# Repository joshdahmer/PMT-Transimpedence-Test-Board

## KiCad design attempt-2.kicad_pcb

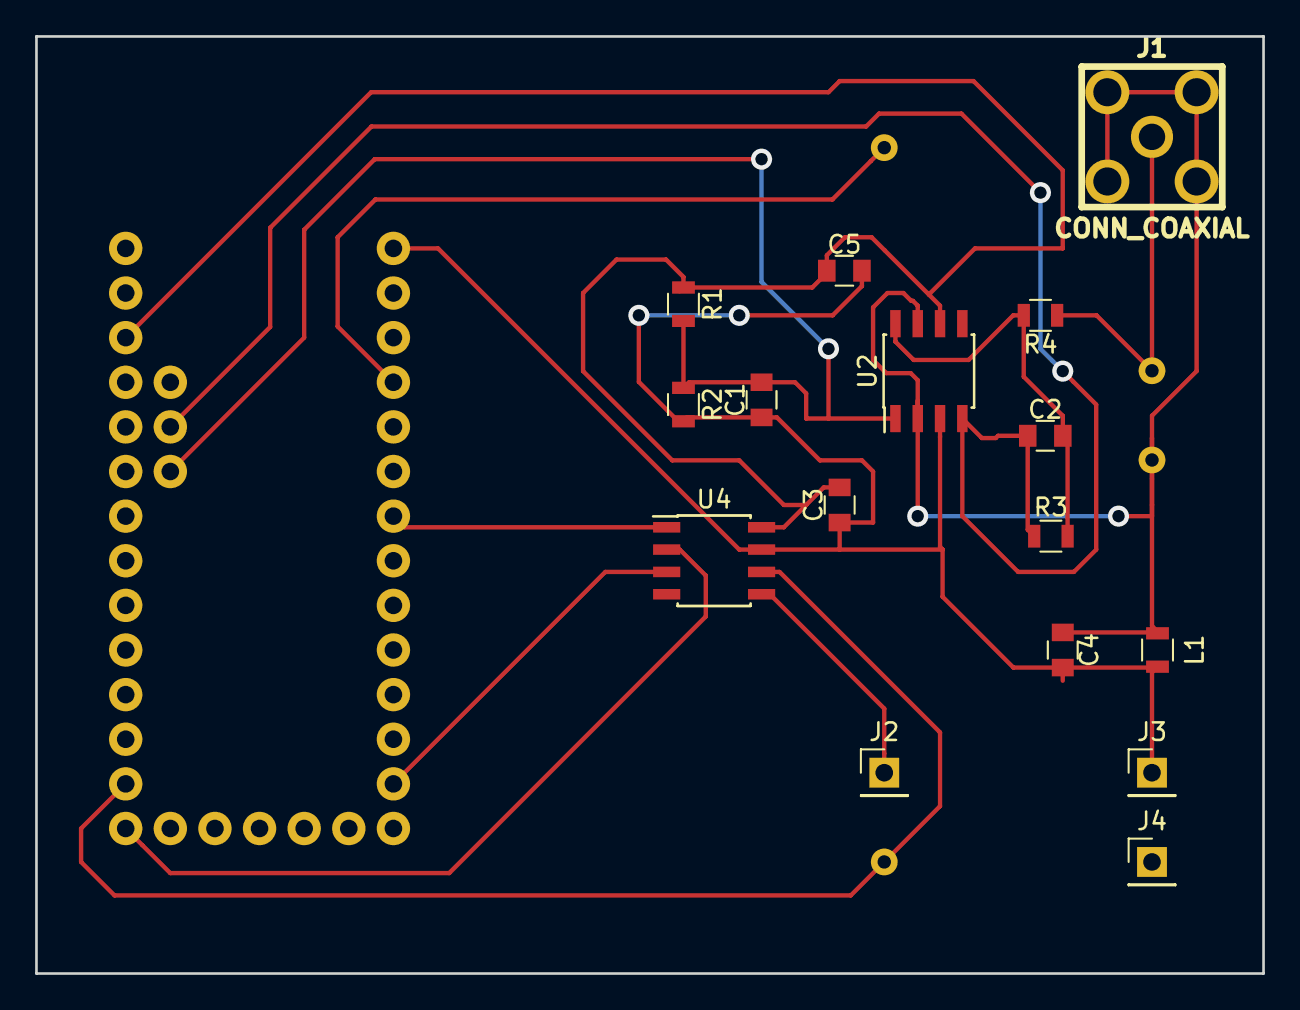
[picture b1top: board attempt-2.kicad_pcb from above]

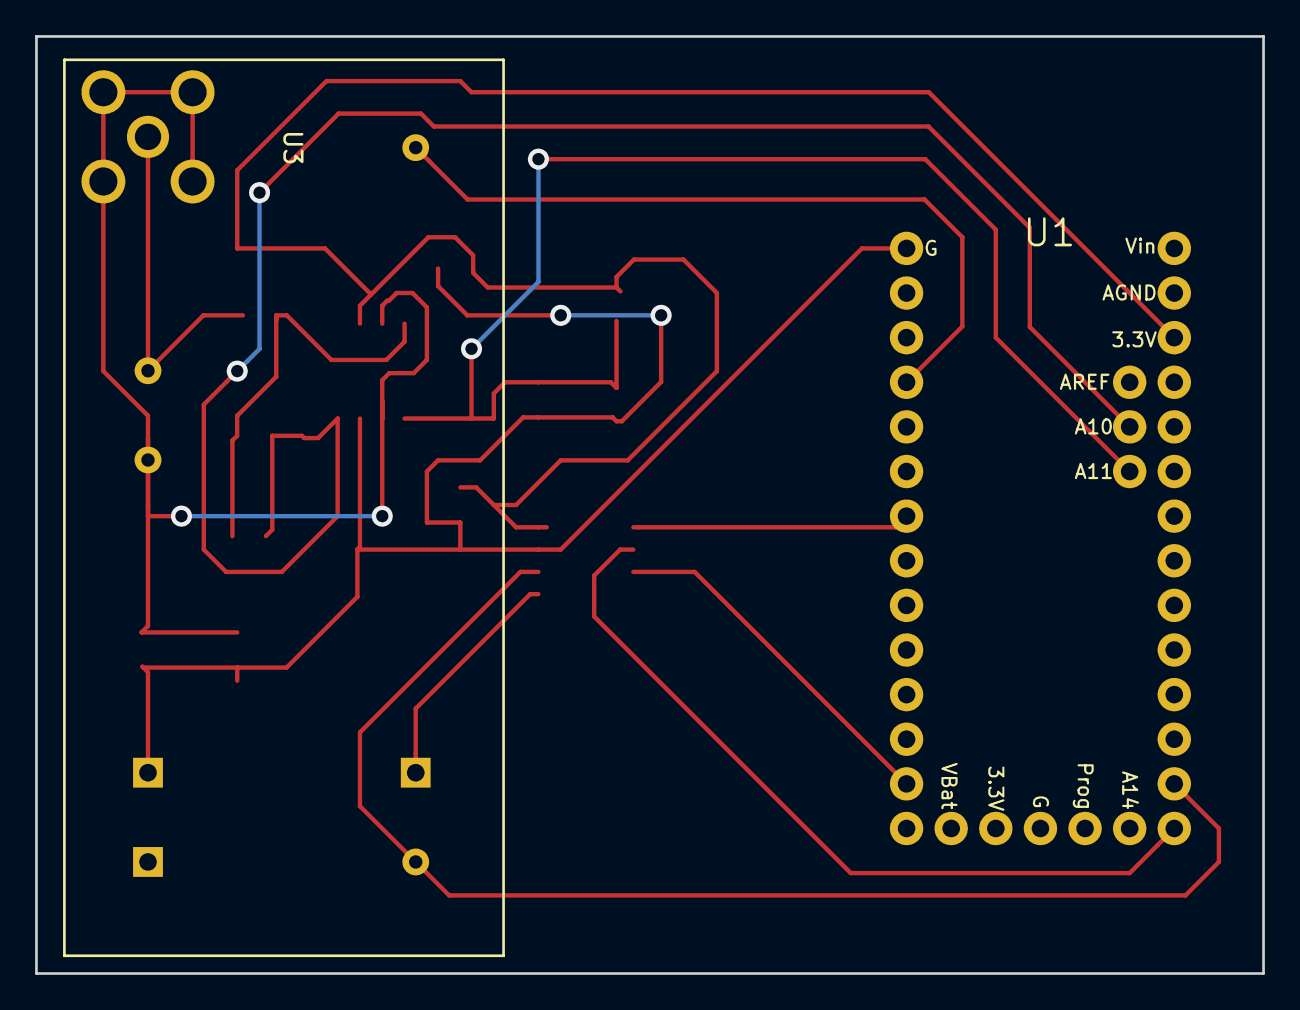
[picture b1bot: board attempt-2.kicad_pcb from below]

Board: 2 copper layers, 69.8 x 53.3 mm, 18 parts (2 on the bottom side), 14 nets.

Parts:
C1, C3, C4, C5: 0.1uF; C_0805
C2: 200p; C_0805
J1: CONN_COAXIAL; JACK_SMA
J2, J3, J4: CONN_01X01; Pin_Header_Straight_1x01_Pitch2.54mm
L1: Ferrite_Bead; L_0805
R1, R4: 10k; R_0805
R2: 3.3k; R_0805
R3: 30k; R_0805
U1: Teensy_3.2; Teensy-3.2
U2: LMP7721; SOIC-8_3.9x4.9mm_Pitch1.27mm
U3: H12056-PMT
U4: MCP41050; SOIC-8_3.9x4.9mm_Pitch1.27mm

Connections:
+1.2V: J2.1, U3.2, U4.5
+3.3V: C3.2, C5.1, R1.1, U1.24, U2.6, U4.8
+5V(VUSB): J4.1, U3.4
ADC: C2.1, R3.1, U1.34, U2.4
CS_POT: U1.5, U4.1
DOUT: U1.11, U4.3
GND: C1.1, C3.1, C4.2, C5.2, J3.1, L1.2, R2.2, U1.27, U2.3, U3.5, U4.4, U4.7
MONITOR: U1.14, U3.3, U4.6
unnamed: C2.2, R3.2, R4.2, U2.8
unnamed: C4.1, J1.2, L1.1, U2.2, U2.7, U3.6
unnamed: J1.1, R4.1, U3.7
SCK: U1.13, U4.2
SHUTTER: U1.2, U3.1
VREF: C1.2, R1.2, R2.1, U1.33, U2.1
